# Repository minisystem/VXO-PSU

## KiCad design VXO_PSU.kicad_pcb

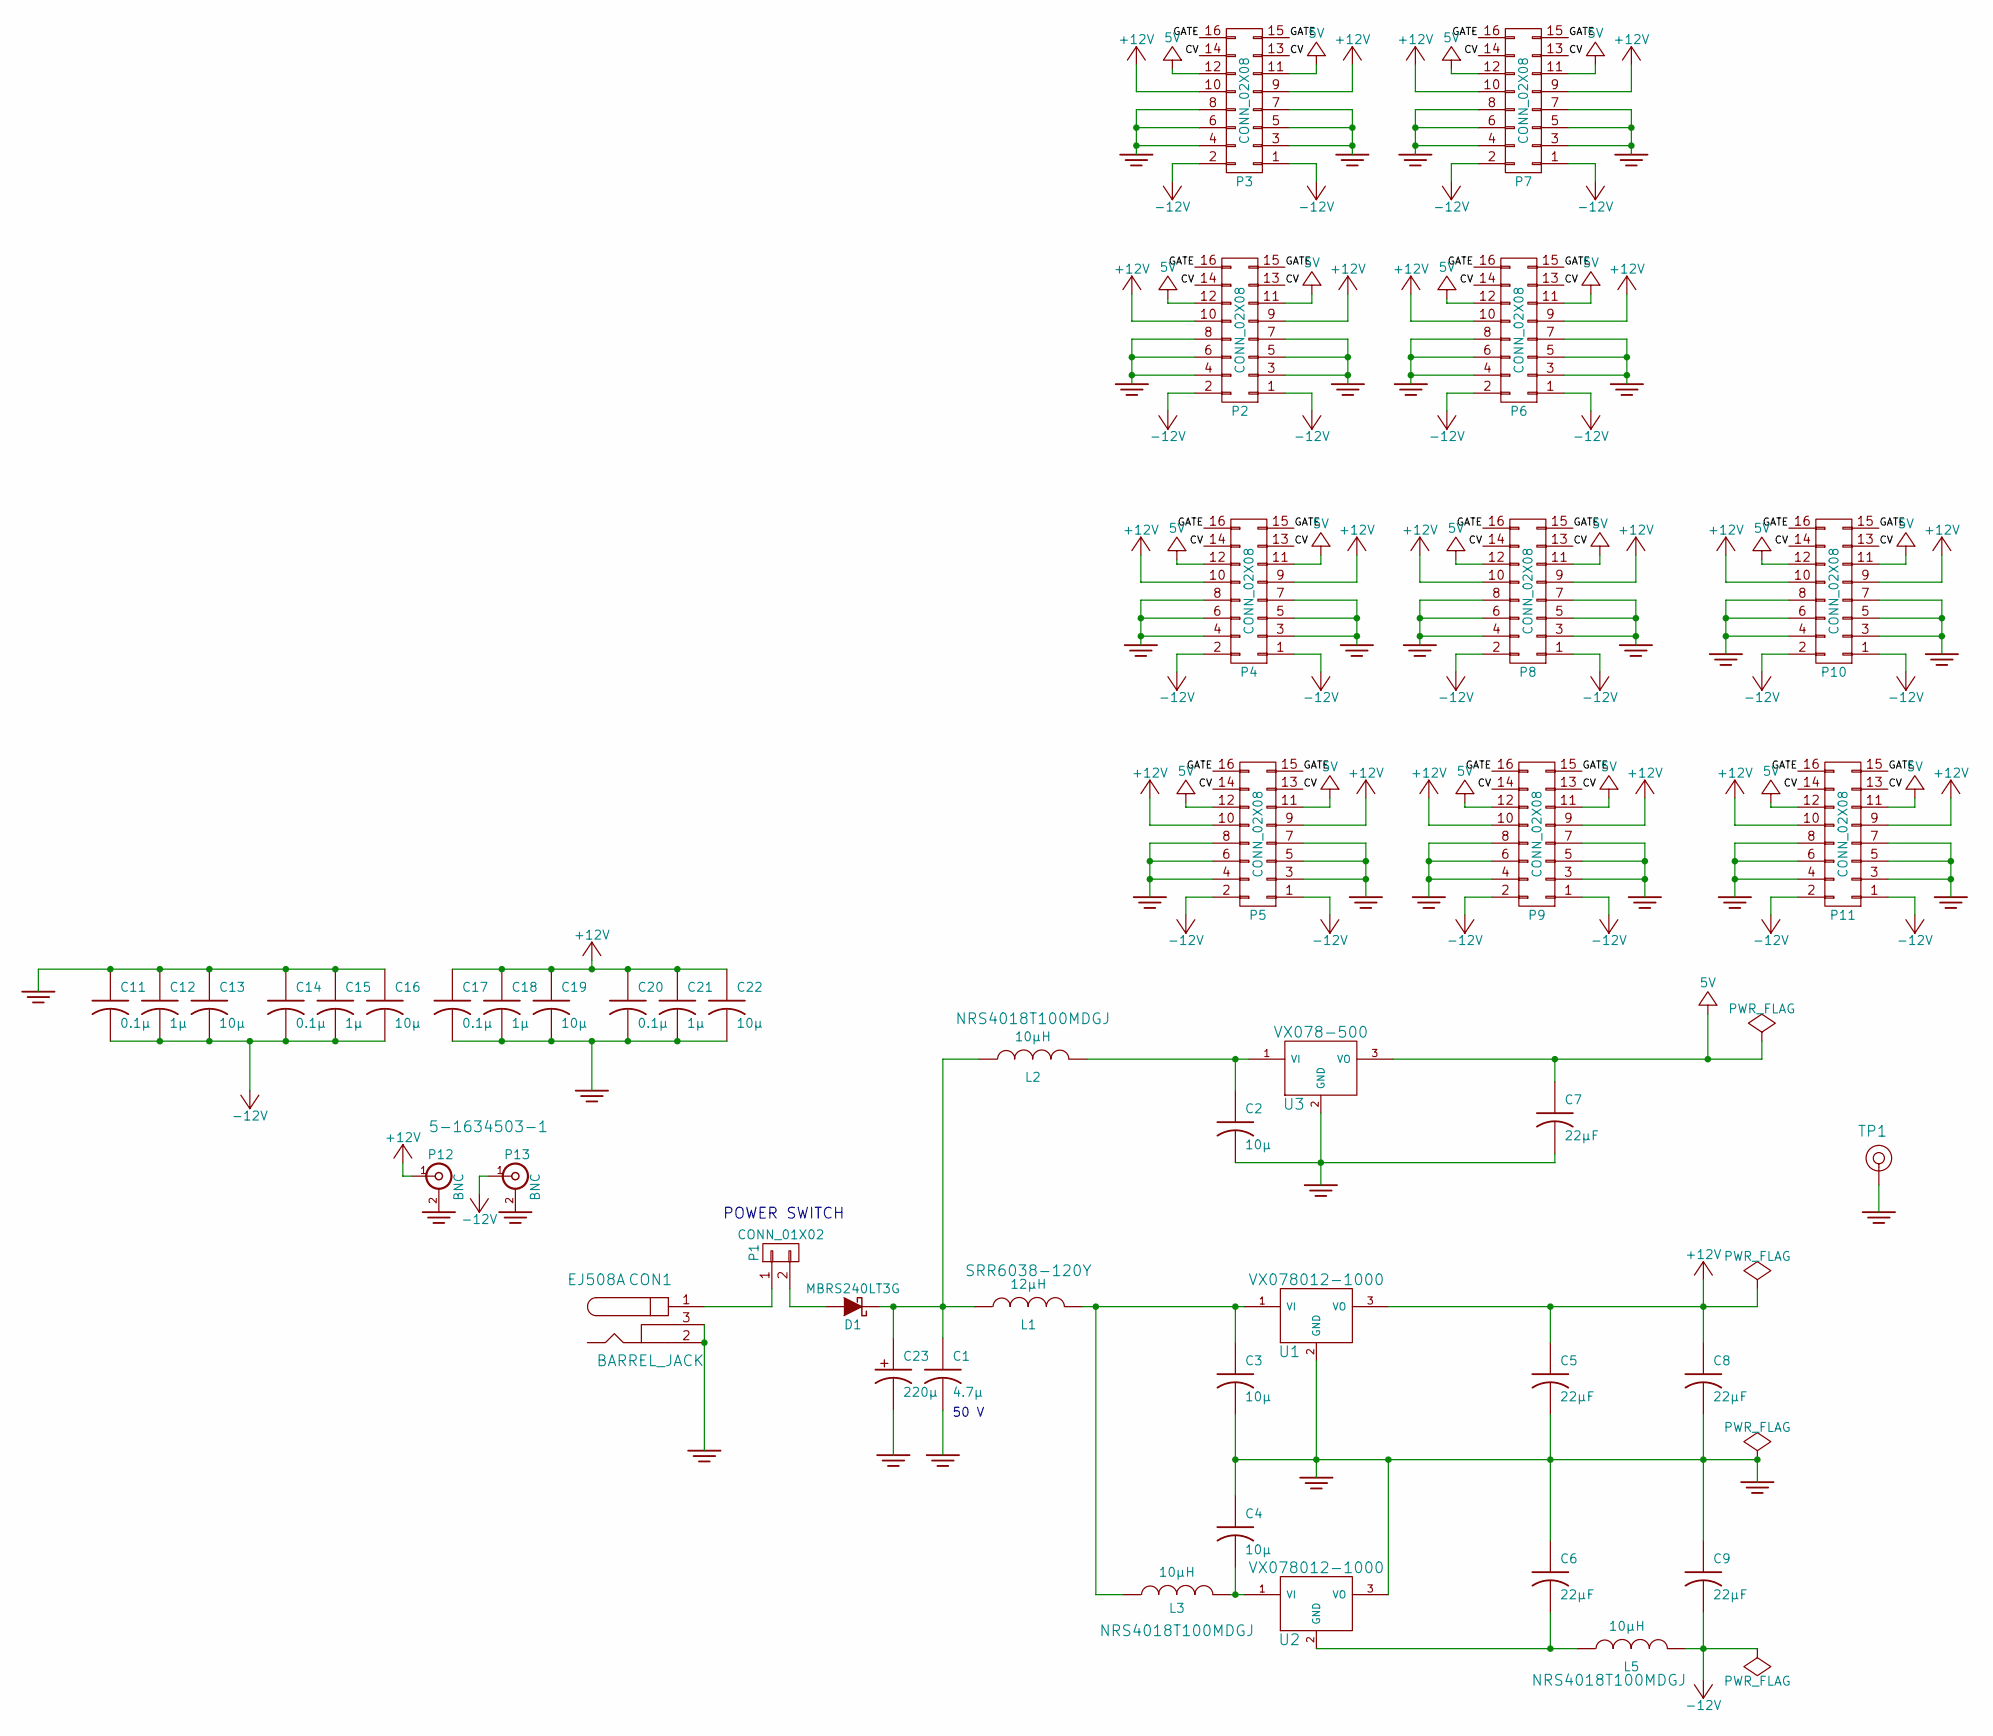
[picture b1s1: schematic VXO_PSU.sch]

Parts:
C1: 4.7µ; C_1206
C2, C3, C4, C13, C16, C19, C22: 10µ; C_1206
C5, C6, C7, C8, C9: 22µF; C_1206
C11, C14, C17, C20: 0.1µ; C_0603
C12, C15, C18, C21: 1µ; C_0805
C23: 220µ; CP_Radial_D8.0mm_P3.50mm
CON1: BARREL_JACK; 2.1-MM-DC-EJ508A; Part Number ‎EJ508A‎
D1: MBRS240LT3G; SMB-1C2A
L1: 12µH; SRR6038-120Y; Part Number SRR6038-120Y
L2, L3, L5: 10µH; L_Taiyo-Yuden_NR-40xx
P1: CONN_01X02; Pin_Header_Straight_1x02_Pitch2.54mm
P2, P3, P4, P5, P6, P7, P8, P9, P10, P11: CONN_02X08; vasch_strip_8x2
P12: BNC; 5-1634503-1_BNC_PCB; Part Number 5-1634503-1‎
P13: BNC; 5-1634503-1_BNC_PCB
TP1: CONN_1; TEST_POINT_LOOP_4592
U1, U2: VX078012-1000; CONV_VXO78012-1000
U3: VX078-500; CUI_VXO780XX-500

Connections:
+5V: C7.1, P2.11, P2.12, P3.11, P3.12, P4.11, P4.12, P5.11, P5.12, P6.11, P6.12, P7.11, P7.12, P8.11, P8.12, P9.11, P9.12, P10.11, P10.12, P11.11, P11.12, U3.3 (VO)
+12V: C5.1, C8.1, C17.1, C18.1, C19.1, C20.1, C21.1, C22.1, P2.9, P2.10, P3.9, P3.10, P4.9, P4.10, P5.9, P5.10, P6.9, P6.10, P7.9, P7.10, P8.9, P8.10, P9.9, P9.10, P10.9, P10.10, P11.9, P11.10, P12.1 (In), U1.3 (VO)
-12V: C9.2, C11.2, C12.2, C13.2, C14.2, C15.2, C16.2, L5.2, P2.1, P2.2, P3.1, P3.2, P4.1, P4.2, P5.1, P5.2, P6.1, P6.2, P7.1, P7.2, P8.1, P8.2, P9.1, P9.2, P10.1, P10.2, P11.1, P11.2, P13.1 (In)
/CV: P2.13, P2.14, P3.13, P3.14, P4.13, P4.14, P5.13, P5.14, P6.13, P6.14, P7.13, P7.14, P8.13, P8.14, P9.13, P9.14, P10.13, P10.14, P11.13, P11.14
/GATE: P2.15, P2.16, P3.15, P3.16, P4.15, P4.16, P5.15, P5.16, P6.15, P6.16, P7.15, P7.16, P8.15, P8.16, P9.15, P9.16, P10.15, P10.16, P11.15, P11.16
GND: C1.2, C2.2, C3.2, C4.1, C5.2, C6.1, C7.2, C8.2, C9.1, C11.1, C12.1, C13.1, C14.1, C15.1, C16.1, C17.2, C18.2, C19.2, C20.2, C21.2, C22.2, C23.2 (-), CON1.2, CON1.3, P2.3, P2.4, P2.5, P2.6, P2.7, P2.8, P3.3, P3.4, P3.5, P3.6, P3.7, P3.8, P4.3, P4.4, P4.5, P4.6, P4.7, P4.8, P5.3, P5.4, P5.5, P5.6, P5.7, P5.8, P6.3, P6.4, P6.5, P6.6, P6.7, P6.8, P7.3, P7.4, P7.5, P7.6, P7.7, P7.8, P8.3, P8.4, P8.5, P8.6, P8.7, P8.8, P9.3, P9.4, P9.5, P9.6, P9.7, P9.8, P10.3, P10.4, P10.5, P10.6, P10.7, P10.8, P11.3, P11.4, P11.5, P11.6, P11.7, P11.8, P12.2 (Ext), P13.2 (Ext), TP1.1, U1.2 (GND), U2.3 (VO), U3.2 (GND)
unnamed: C1.1, C23.1 (+), D1.1 (K), L1.1, L2.1
unnamed: C2.1, L2.2, U3.1 (VI)
unnamed: C3.1, L1.2, L3.1, U1.1 (VI)
unnamed: C4.2, L3.2, U2.1 (VI)
unnamed: C6.2, L5.1, U2.2 (GND)
unnamed: CON1.1, P1.1
unnamed: D1.2 (A), P1.2

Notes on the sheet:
POWER SWITCH
50 V

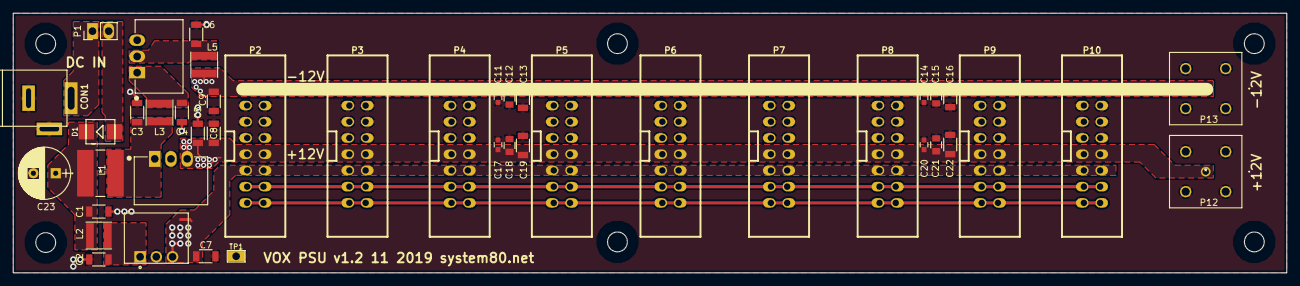
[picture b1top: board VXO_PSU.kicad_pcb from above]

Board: 4 copper layers, 199.4 x 40.6 mm, 50 parts (0 on the bottom side), 13 nets.

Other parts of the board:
HOLE-M3, HOLE-M3#2, HOLE-M3#3, HOLE-M3#4, HOLE-M3#5, HOLE-M3#6: VAL**; HOLE-M3

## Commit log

2019-10-18 ordered prototype board with BNC connectors for testing
2019-11-01 rework to verson 1.1, changing inductors, removing pi output filters
2019-11-02 new 4 layer board updated, routed
2019-11-02 six layers
2019-11-02 tweak. ready to order probably
2019-11-03 fiddly tricks
2019-11-05 this commit reverts back to 4layer. boards ordered
2019-11-16 added back negative rail pi filter, changed input L footprint
2019-11-17 VOX PSU renamed. few more tweaks then ready for PCB ordering
2020-10-10 not sure what last status was. don't think 1.2 was ever ordreed but corrected problems with 1.1 maybe

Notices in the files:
parts and their libraries:
Copyright 2016 Accelerated Designs. All rights reserved.
